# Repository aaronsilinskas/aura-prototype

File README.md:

# Aura Prototype

The prototype firmware and game engine for **Aura**, a platform for interactive
adventure games played in the real world with handheld devices and props that light
up, make sound, and react to how you play. Aura is being built by
[Mindwidgets](https://mindwidgets.com); the site explains what Aura is and
[how it works today](https://mindwidgets.com/aura/how-it-works/).

This repository is where the software is worked out: a game engine that turns
buttons, motion, infrared, and radio into games, and an animation engine for the
lights, sound, and vibration players get back. It is written in Python and runs on
[CircuitPython](https://circuitpython.org/) microcontrollers, and most of it also
runs on a desktop so it can be tested without hardware.

---

## Status

Aura is in prototype. This is working code under active development, not a kit.

- **You can't buy or build an Aura device yet.** There are no build instructions,
  parts list, or finished circuit board designs here. `electronics/` holds only
  rough sketches so far. The prototype is hand-wired from off-the-shelf breakout
  boards.
- **You can read the code, run the tests, and watch the effects in a terminal**
  without any hardware. See [Try it without hardware](#try-it-without-hardware).
- **The games are in `packs/scenes/`**, one folder per scene, alongside scenes for
  testing hardware and browsing effects.

Issues and pull requests are not being sought yet. To hear when there is something
to build or play, sign up at [mindwidgets.com](https://mindwidgets.com).

---

## What is in here

```
effects/      Composable animation engine for lights, sound, and vibration
engine/       Event-driven game loop: rules, scenes, state, packs, and I/O abstractions
packs/        Shared effects and rules, and the scenes (games) built from them
magic/        Spell and aura game logic (elements, buffs and debuffs, cast types)
hardware/     CircuitPython drivers and the hardware abstractions above them
app/          Wires the engine to the hardware and runs a scene on a device
examples/     Entry points: a desktop terminal demo and the on-device scene runner
scripts/      Deploy and maintenance scripts that run on the desktop
electronics/  Circuit board designs (rough sketches only, so far)
docs/         Domain map and architecture decision records (the glossary is GLOSSARY.md)
```

A few words used throughout the code:

- A **rule** is how a game responds to player input, communications, and time.
- An **effect** is what players see, hear, and feel.
- A **scene** is a game: the rules and effects that combine into it.
- A **pack** is a set of rules or effects that more than one scene can use. The
  elemental magic effects (fire, water, lightning, and the rest) are a pack.

See [`docs/domain.md`](docs/domain.md) for key types and constraints, and
[`GLOSSARY.md`](GLOSSARY.md) for the full glossary.

---

## Try it without hardware

You need Python 3.10 or newer and [uv](https://docs.astral.sh/uv/).

```sh
uv sync            # install the development tools
uv run pytest      # run the test suite
```

To watch the effects engine run, start the terminal demo from the repository root
(macOS or Linux, in a terminal with 24-bit color):

```sh
PYTHONPATH=. uv run python examples/ansi-multi-effect-demo.py
```

Press `a` for fire, `b` for water, `c` for lightning, `d` to stop them all, and `q`
to quit.

---

## Hardware the prototype uses

There is no single finished device. The firmware builds whichever of these parts the
device's config file declares, and leaves out the rest:

| Part | What the code supports |
|------|------------------------|
| Microcontroller | RP2350 with PSRAM, running CircuitPython 10. Pimoroni's Pico 2 boards with PSRAM work well, for example the [Pico Plus 2](https://shop.pimoroni.com/products/pimoroni-pico-plus-2) or [Pico LiPo 2](https://shop.pimoroni.com/products/pimoroni-pico-lipo-2). A standard Raspberry Pi Pico 2 has no PSRAM and will not work |
| Lights | IS31FL3741 13×9 RGB LED matrix, NeoPixel strips |
| Sound | I2S audio output |
| Vibration | DRV2605L haptic driver |
| Motion | LIS3DH accelerometer, MMC5603 magnetometer |
| Buttons | Any GPIO pins |
| Infrared | Up to three emitters (line, cone, and area) and one or more receivers |
| Radio | RFM69HCW at 915 MHz |
| Storage | SD card over SPI |

The infrared and radio links were tested with two separate tools,
[infrared-analyzer](https://github.com/aaronsilinskas/infrared-analyzer) and
[rfm69-analyzer](https://github.com/aaronsilinskas/rfm69-analyzer).

---

## Running on a device

These are working notes for a hand-wired prototype, not a build guide.

A device reads two JSON files from the root of its `CIRCUITPY` drive. Both are
required; there are no built-in defaults.

- **`aura-device.json`** declares the hardware: which parts are fitted and which
  pins they use. Each part is built only if its section is present and enabled.
  [`examples/aura-device.pico-2.json`](examples/aura-device.pico-2.json)
  is a complete example, tested on Pimoroni Pico 2 boards.
  [`examples/aura-device.simulated.json`](examples/aura-device.simulated.json)
  is for the test-only Simulated device, not for flashing to a board.
- **`aura-boot.json`** picks the scene to boot, by its folder name under
  `packs/scenes/`, as in
  [`examples/aura-boot.json`](examples/aura-boot.json):
  `{"default_scene": "hardware_test"}`.

  If the device has an SD card, a scene saved to the card's `aura-state.json`
  takes priority over `default_scene`.

To put the code on a board:

1. Install CircuitPython 10 on the board, and copy the Adafruit libraries for the
   parts you declared into `CIRCUITPY/lib/`.
2. Download the matching `mpy-cross` compiler: `scripts/setup_mpy_cross.sh`
3. Copy both JSON files to the `CIRCUITPY` drive.
4. Deploy the scene runner and all modules:

   ```sh
   uv run python -m scripts.deploy examples/hardware/scene_demo.py
   ```

   The board reboots and starts the scene.

### `aura-device.json` in brief

```json
{
  "pixels": [
    {
      "type": "matrix",
      "cols": 13,
      "scope_rows": {
        "global.buff": [0, 1], "global.debuff": [1, 2], "global.main": [2, 5],
        "personal": [5, 7], "directional": [7, 8], "ambient": [8, 9]
      }
    }
  ],
  "buttons": ["GP26", "GP27"],
  "ir": {
    "rx": "GP13",
    "line": "GP10",
    "cone": "GP11",
    "area_of_effect": "GP12"
  },
  "audio": {
    "voices": 2,
    "max_volume": 0.1,
    "i2s_bit_clock": "GP7",
    "i2s_word_select": "GP8",
    "i2s_data": "GP6"
  }
}
```

- **`pixels`** is a list of light outputs. `type` is `"matrix"` (IS31FL3741, at most
  one) or `"neopixel"`. Each entry maps **scopes**, the named regions an effect can
  be shown in, to rows of the matrix (`scope_rows`) or to pixel ranges of a strip
  (`scope_pixels`).
- **`buttons`** is a list of board pin names.
- **`ir`** takes `rx` (one receiver pin, or a list of them) and at least a `line`
  emitter; `cone` and `area_of_effect` emitters are optional. Each scene chooses
  the infrared message format it uses: Aura's own by default, or the `tag` scene's
  format, which works with off-the-shelf infrared tag gear.
- **`audio`** takes `voices` (how many sounds can play at once), `max_volume`
  (0.0 to 1.0), and the three I2S pins.

The example file also shows the `accelerometer`, `magnetometer`, `haptics`, `radio`,
`sdcard`, `i2c`, `spi`, and `neopixel_current_budget` sections.
`neopixel_current_budget` is optional: when the NeoPixel strips could draw more than
`current_limit_ma` at full white, the device dims them at boot to fit, never below
`min_brightness`.

---

## How the engine works

### Event flow

```
(InputEvent | NetworkEvent)
        │
        ▼
   SceneRun               one per running scene: its GameState + rules in dispatch order
        │  run.tick(elapsed)
        ▼
   GameRule.handle_event(event, state)
        │  rules read/write state.get/state.set, queue new events,
        │  call state.effect_controls, call state.scene_controls
        ▼
   EffectManager          routes effects to EffectOutput by scope
        │
        ▼
   EffectOutput           hardware: lights, audio, haptics
```

Rules are stateless: all mutable game data lives in the scene's `GameState`.
Rules fire effects through `state.effect_controls`, read Settings through
`state.settings`, and leave or cover the scene through `state.scene_controls`.

### Packs and scenes

Each folder under `packs/` with a manifest is a pack, and each folder under
`packs/scenes/` is a scene. One scan at boot finds them all and checks every
declaration, so a bad pack or scene fails before anything runs. Pack items are
imported only when first used.

- **Effect pack**: manifest `effects.json`; each `.py` file exports `BUILD`, a
  `(config) → Effect` callable. Effects are named `"pack.effect"`, e.g.
  `"elements.fire"`.
- **Rule pack**: manifest `rules.json`; each `.py` file exports `RULE`, a
  `GameRule` instance. Its manifest can also declare **Settings** and the
  **Capabilities** the rules need:

```json
{
  "version": "1.0",
  "requires": ["button.A", "button.B"],
  "settings": {
    "hold_seconds": {"type": "float", "default": 5.0, "description": "Seconds to hold."}
  }
}
```

A scene is described by its `scene.json`:

```json
{
  "version": "1.0",
  "effect_packs": [{"name": "elements", "version": "1.0"}],
  "rule_packs": [
    {"name": "return_to_lobby", "version": "2.0", "settings": {"hold_seconds": 2.0}}
  ],
  "settings": {
    "window_seconds": {"type": "float", "default": 3.0, "description": "Seconds per window."}
  },
  "requires": ["accelerometer"],
  "ir_codec": "aura"
}
```

| Key | Meaning |
|-----|---------|
| `version` | The scene's own `MAJOR.MINOR` version |
| `effect_packs`, `rule_packs` | Packs in load order. Each `version` is the minimum compatible one: same major, installed minor at least this. A rule pack reference may override that pack's Settings |
| `settings` | Optional. The scene's own Settings, in the manifest's shape |
| `requires` | Optional. Capabilities the scene can't be played without, on top of its rule packs' |
| `ir_codec` | Optional. The infrared message format: `"aura"` (default) or `"tag"` |

A Setting's `type` is `int`, `float`, `bool`, `str` or `list`. One with no
`default` must be set by every scene that uses the pack. Rules read Settings with
`state.settings.get_float("scene", "window_seconds")` and its siblings, by
namespace (`"scene"` or the pack's name).

A **Capability** is hardware a scene can depend on: `button.A` … `button.Z`
(labelled in the order `buttons` lists them), `ir.line`, `ir.cone`,
`ir.area_of_effect`, `ir.receive`, `radio`, `storage`, `accelerometer`,
`magnetometer`. A scene is checked against the device only when it is about to
run. A scene that copes without some hardware leaves it out of `requires` and
asks `state.capabilities.has(name)` instead.

Scenes switch only by rebooting the device into the next one. An **Overlay**
covers a scene for a while and hands it back intact.

The meaning of each term, the versioning rules, and the reasoning behind these
choices are in [`GLOSSARY.md`](GLOSSARY.md) and the ADRs in
[`docs/adr/`](docs/adr/), notably
[ADR-0003](docs/adr/0003-settings-are-declared-as-data-and-checked-at-scan.md)
(Settings),
[ADR-0004](docs/adr/0004-capabilities-are-checked-when-a-scene-is-about-to-run.md)
(Capabilities) and
[ADR-0005](docs/adr/0005-scenes-switch-only-by-reboot.md) (scene switching).

---

## Licensing

This repo splits licensing by area:

- **Software** (`effects/`, `engine/`, `magic/`, `packs/`, `hardware/`, `app/`, `scripts/`, …) —
  [MIT](LICENSE).
- **Hardware designs** (`electronics/`) — CERN-OHL-P-2.0, governed by
  `electronics/LICENSE`.
- **Documentation** (`docs/`) — [CC-BY-4.0](docs/LICENSE).

Each area's `LICENSE` file is authoritative for its scope; `pyproject.toml` declares the
software license for tooling. No per-file license headers are used.

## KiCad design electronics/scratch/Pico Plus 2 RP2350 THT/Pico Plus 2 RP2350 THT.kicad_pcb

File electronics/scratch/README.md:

# Scratch

Freeform experimentation space for electronics design-in-progress — quick sketches,
half-finished schematics, part comparisons, wiring notes, anything that helps while
figuring out what a board should be.

**Nothing in this directory is authoritative.** Nothing here is guaranteed to be
correct, complete, buildable, or even kept up to date. A design in `scratch/` has no
fab tag, no revision folder, and no promise of a `rev<X>/` promotion.

Once a sketch here graduates into an intended real board, it is **promoted** into
`pcbs/<pcb>/rev<X>/` — at that point the `pcbs/` copy is the source of record, and
whatever is left behind in `scratch/` stays non-authoritative. See
`../pcbs/README.md` for the promotion and revision-lifecycle conventions.

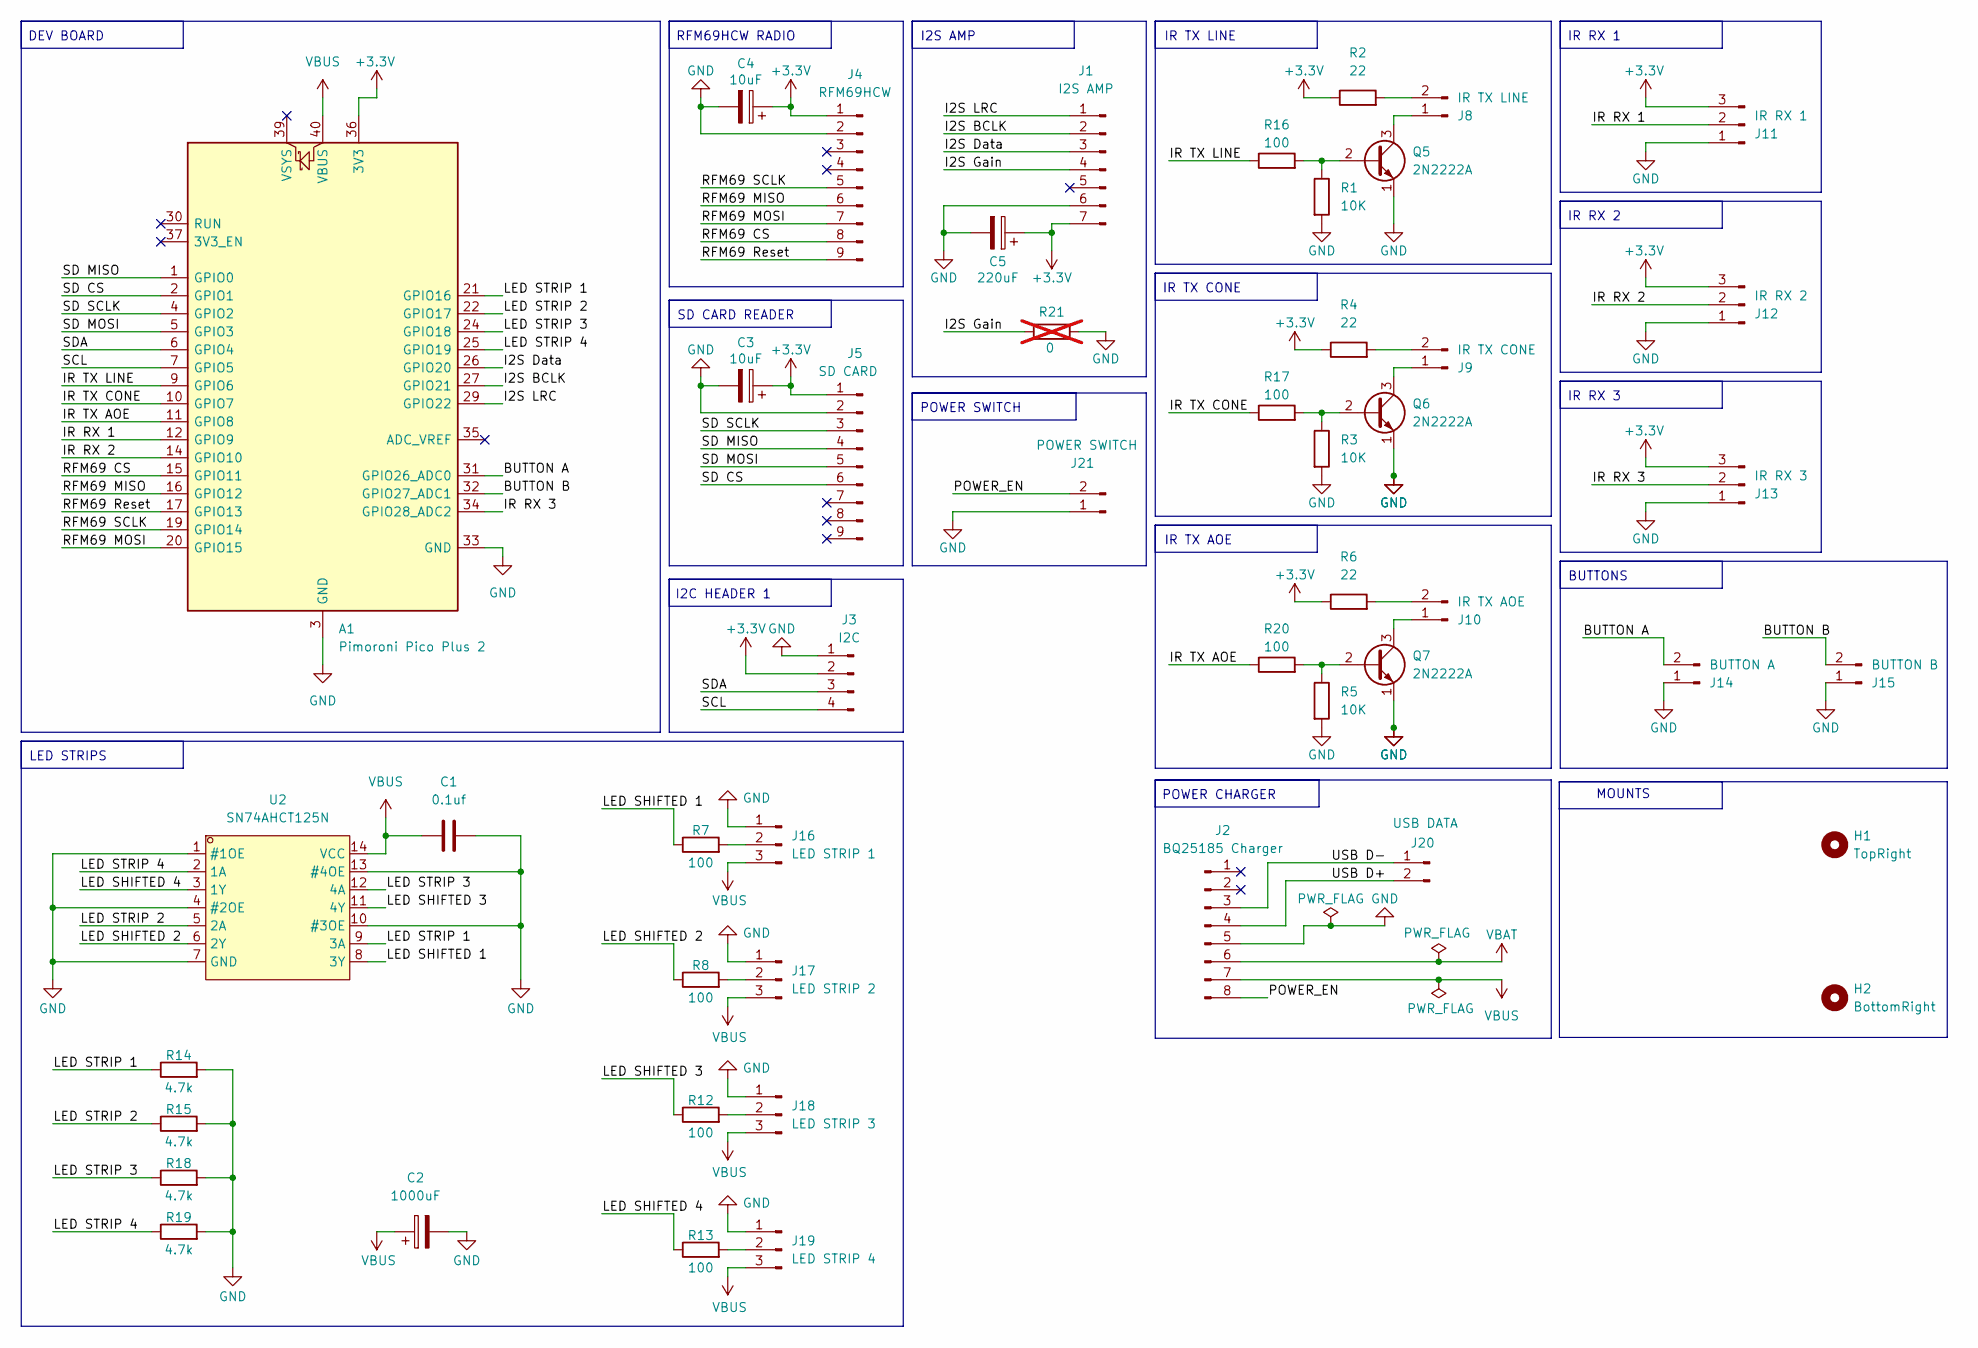
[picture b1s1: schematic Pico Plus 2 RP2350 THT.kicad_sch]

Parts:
A1: Pimoroni Pico Plus 2; RaspberryPi_Pico_Common_Unspecified
C1: 0.1uf; C_Disc_D5.0mm_W2.5mm_P5.00mm
C2: 1000uF; CP_Radial_D8.0mm_P3.80mm
C3, C4: 10uF; CP_Radial_D5.0mm_P2.00mm
C5: 220uF; CP_Radial_D6.3mm_P2.50mm
H1: TopRight; MountingHole_3.2mm_M3_DIN965_Pad
H2: BottomRight; MountingHole_3.2mm_M3_DIN965_Pad
J1: I2S AMP; PinHeader_1x07_P2.54mm_Vertical
J2: BQ25185 Charger; PinHeader_1x08_P2.54mm_Vertical
J3: I2C; PinHeader_1x04_P2.54mm_Vertical
J4: RFM69HCW; PinHeader_1x09_P2.54mm_Vertical
J5: SD CARD; PinHeader_1x09_P2.54mm_Vertical
J8: IR TX LINE; PinHeader_1x02_P2.54mm_Vertical
J9: IR TX CONE; PinHeader_1x02_P2.54mm_Vertical
J10: IR TX AOE; PinHeader_1x02_P2.54mm_Vertical
J11: IR RX 1; PinHeader_1x03_P2.54mm_Vertical
J12: IR RX 2; PinHeader_1x03_P2.54mm_Vertical
J13: IR RX 3; PinHeader_1x03_P2.54mm_Vertical
J14: BUTTON A; PinHeader_1x02_P2.54mm_Vertical
J15: BUTTON B; PinHeader_1x02_P2.54mm_Vertical
J16: LED STRIP 1; PinHeader_1x03_P2.54mm_Vertical
J17: LED STRIP 2; PinHeader_1x03_P2.54mm_Vertical
J18: LED STRIP 3; PinHeader_1x03_P2.54mm_Vertical
J19: LED STRIP 4; PinHeader_1x03_P2.54mm_Vertical
J20: USB DATA; PinHeader_1x02_P2.54mm_Vertical
J21: POWER SWITCH; PinHeader_1x02_P2.54mm_Vertical
Q5, Q6, Q7: 2N2222A; TO-92_Inline
R1, R3, R5: 10K; R_Axial_DIN0207_L6.3mm_D2.5mm_P10.16mm_Horizontal
R2, R4, R6: 22; R_Axial_DIN0207_L6.3mm_D2.5mm_P10.16mm_Horizontal
R7, R8, R12, R13, R16, R17, R20: 100; R_Axial_DIN0207_L6.3mm_D2.5mm_P10.16mm_Horizontal
R14, R15, R18, R19: 4.7k; R_Axial_DIN0207_L6.3mm_D2.5mm_P10.16mm_Horizontal
R21: 0; R_Axial_DIN0207_L6.3mm_D2.5mm_P10.16mm_Horizontal; not fitted
U2: SN74AHCT125N; PDIP-14_L19.3-W6.4-P2.54-LS7.6-BL; MPN SN74AHCT125N; LCSC Part C354152

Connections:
+3.3V: A1.36 (3V3), C3.1, C4.1, C5.1, J1.7, J3.2, J4.1, J5.1, J11.3, J12.3, J13.3, R2.1, R4.1, R6.1
/BUTTON A: A1.31 (GPIO26_ADC0), J14.2
/BUTTON B: A1.32 (GPIO27_ADC1), J15.2
/I2S BCLK: A1.27 (GPIO21), J1.2
/I2S Data: A1.26 (GPIO20), J1.3
/I2S Gain: J1.4, R21.1
/I2S LRC: A1.29 (GPIO22), J1.1
/IR RX 1: A1.12 (GPIO9), J11.2
/IR RX 2: A1.14 (GPIO10), J12.2
/IR RX 3: A1.34 (GPIO28_ADC2), J13.2
/IR TX AOE: A1.11 (GPIO8), R20.1
/IR TX CONE: A1.10 (GPIO7), R17.1
/IR TX LINE: A1.9 (GPIO6), R16.1
/LED SHIFTED 1: R7.1, U2.8 (3Y)
/LED SHIFTED 2: R8.1, U2.6 (2Y)
/LED SHIFTED 3: R12.1, U2.11 (4Y)
/LED SHIFTED 4: R13.1, U2.3 (1Y)
/LED STRIP 1: A1.21 (GPIO16), R14.1, U2.9 (3A)
/LED STRIP 2: A1.22 (GPIO17), R15.1, U2.5 (2A)
/LED STRIP 3: A1.24 (GPIO18), R18.1, U2.12 (4A)
/LED STRIP 4: A1.25 (GPIO19), R19.1, U2.2 (1A)
/POWER_EN: J2.8, J21.2
/RFM69 CS: A1.15 (GPIO11), J4.8
/RFM69 MISO: A1.16 (GPIO12), J4.6
/RFM69 MOSI: A1.20 (GPIO15), J4.7
/RFM69 Reset: A1.17 (GPIO13), J4.9
/RFM69 SCLK: A1.19 (GPIO14), J4.5
/SCL: A1.7 (GPIO5), J3.4
/SD CS: A1.2 (GPIO1), J5.6
/SD MISO: A1.1 (GPIO0), J5.4
/SD MOSI: A1.5 (GPIO3), J5.5
/SD SCLK: A1.4 (GPIO2), J5.3
/SDA: A1.6 (GPIO4), J3.3
/USB D+: J2.4, J20.2
/USB D-: J2.3, J20.1
GND: A1.3 (GND), A1.8 (GND), A1.13 (GND), A1.18 (GND), A1.23 (GND), A1.28 (GND), A1.33 (GND), A1.38 (GND), C1.2, C2.2, C3.2, C4.2, C5.2, J1.6, J2.5, J3.1, J4.2, J5.2, J11.1, J12.1, J13.1, J14.1, J15.1, J16.1, J17.1, J18.1, J19.1, J21.1, Q5.1 (E), Q6.1 (E), Q7.1 (E), R1.2, R3.2, R5.2, R14.2, R15.2, R18.2, R19.2, R21.2, U2.1 (#1OE), U2.4 (#2OE), U2.7 (GND), U2.10 (#3OE), U2.13 (#4OE)
unnamed: J8.1, Q5.3 (C)
unnamed: J8.2, R2.2
unnamed: J9.1, Q6.3 (C)
unnamed: J9.2, R4.2
unnamed: J10.1, Q7.3 (C)
unnamed: J10.2, R6.2
unnamed: J16.2, R7.2
unnamed: J17.2, R8.2
unnamed: J18.2, R12.2
unnamed: J19.2, R13.2
unnamed: Q5.2 (B), R1.1, R16.2
unnamed: Q6.2 (B), R3.1, R17.2
unnamed: Q7.2 (B), R5.1, R20.2
VBAT: J2.6
VBUS: A1.40 (VBUS), C1.1, C2.1, J2.7, J16.3, J17.3, J18.3, J19.3, U2.14 (VCC)

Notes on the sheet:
RFM69HCW RADIO
I2S AMP
SD CARD READER
IR TX AOE
POWER CHARGER
IR TX LINE
POWER SWITCH
MOUNTS
I2C HEADER 1
IR RX 3
BUTTONS
IR RX 1
LED STRIPS
IR TX CONE
DEV BOARD
IR RX 2

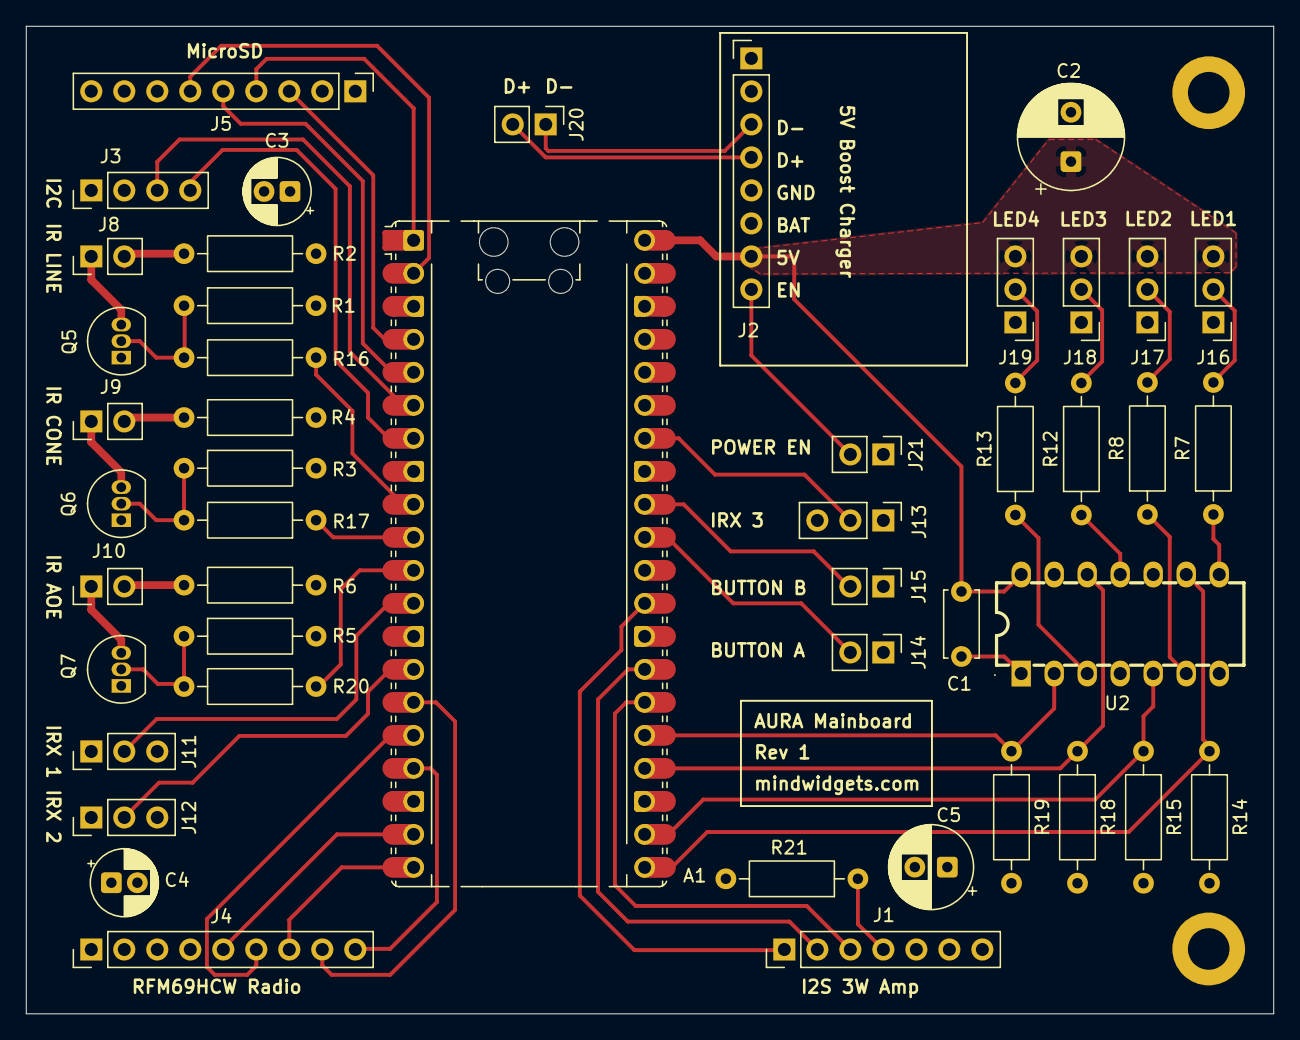
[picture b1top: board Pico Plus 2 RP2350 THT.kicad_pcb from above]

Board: 4 copper layers, 96.0 x 76.0 mm, 49 parts (0 on the bottom side), 50 nets.

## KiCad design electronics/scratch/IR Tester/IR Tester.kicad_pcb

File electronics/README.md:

# Electronics

PCB design source for Aura's custom hardware — schematics, board layouts, shared
symbols/footprints, and fabrication exports. This directory is deliberately separate
from:

- **`hardware/`** (repo root) — the Python firmware package that runs on the props'
  microcontrollers, governed by `ruff`/`import-linter`/`mypy`.
- **CircuitPython's `board` module** — the on-device pin-naming API `hardware/`
  imports at runtime.

`electronics/` contains no Python and is not a package. It carries no import
contracts, isn't touched by `ruff`, `import-linter` or `mypy`, and the Python-only
pre-commit hooks never rewrite the PCB-tool files in here.

Boards are drawn in one of two tools, used as peers: **KiCad** and
**EasyEDA Pro**. Each PCB is committed to a single tool (never mixed within one
board); see `pcbs/README.md`.

---

## Layout

```
electronics/
  README.md      this file — orientation + how to open
  LICENSE        CERN-OHL-P-2.0 (governs everything under electronics/)
  scratch/       freeform, non-authoritative experimentation (see scratch/README.md)
  pcbs/          one subfolder per physical board (see pcbs/README.md)
  libraries/     shared symbols, footprints, and 3D models used across PCBs,
                 split per tool (see libraries/README.md)
```

- **`scratch/`** — sketches and one-off experiments. Nothing in here is
  authoritative; see `scratch/README.md`.
- **`pcbs/`** — the design source of record for every fabricated board, one
  subfolder per PCB. See `pcbs/README.md` for the rev-lifecycle, promotion,
  naming, and fab-tag conventions.
- **`libraries/`** — shared symbol libraries, footprint libraries, and 3D
  models referenced by more than one PCB, so a shared part is edited in one
  place rather than duplicated per board. Split into per-tool subfolders
  (`kicad/`, `easyeda/`) since the two tools' library formats aren't
  interchangeable.

No `<pcb>/` design folders or library files exist yet — this scaffold is
intentionally empty of actual designs.

---

## Revision lifecycle, promotion, and naming (summary)

Full detail lives in `pcbs/README.md`; the short version:

- A **PCB** is the design source for one physical board, named for the board
  itself — never for the prop it ends up in, since a prop and its PCBs are a
  many-to-many relationship (one prop can carry several boards; the same
  board design can serve several props).
- A design **promotes** from `scratch/` into `pcbs/<pcb>/rev<X>/` the moment it
  graduates from sketch to an intended real board. That `rev<X>/` folder is
  then the working directory for the whole design → fab → bring-up → test
  cycle for that revision.
- A genuinely new physical spin of a board is a **new** `rev<X>/` folder
  (`rev2`, `rev3`, …), never an edit-in-place of a prior rev.
- The **rev letter/number goes on the PCB silkscreen**, so the physical board
  and its design folder are always traceable to each other.
- The commit sent to fab is marked with a **git tag** `<pcb>-rev<X>` — the tag,
  not folder immutability, records exactly what was fabricated. Exports are
  hand-generated and refreshed at each fab tag.

---

## How to open

Which tool a board opens in follows its file extensions (`.kicad_*` vs
`.epro`); a board's own folder is drawn in exactly one tool. Tool versions are
pinned so files open without an on-open project upgrade:

- **KiCad** — pinned to **10.0.4** (the latest stable KiCad 10.x release as of
  this writing). Open `pcbs/<pcb>/rev<X>/<pcb>.kicad_pro` in KiCad; schematic
  and PCB editors are reached from there.
- **EasyEDA Pro** — pinned to **3.2**. Open the board's `pcbs/<pcb>/rev<X>/`
  EasyEDA Pro project (`.epro`) in EasyEDA Pro.

> **Note:** no maintainer input was available when this scaffold was created —
> confirm both pinned versions against what the maintainer actually runs, and
> bump these lines deliberately (with a comment on why) whenever the project
> upgrades.

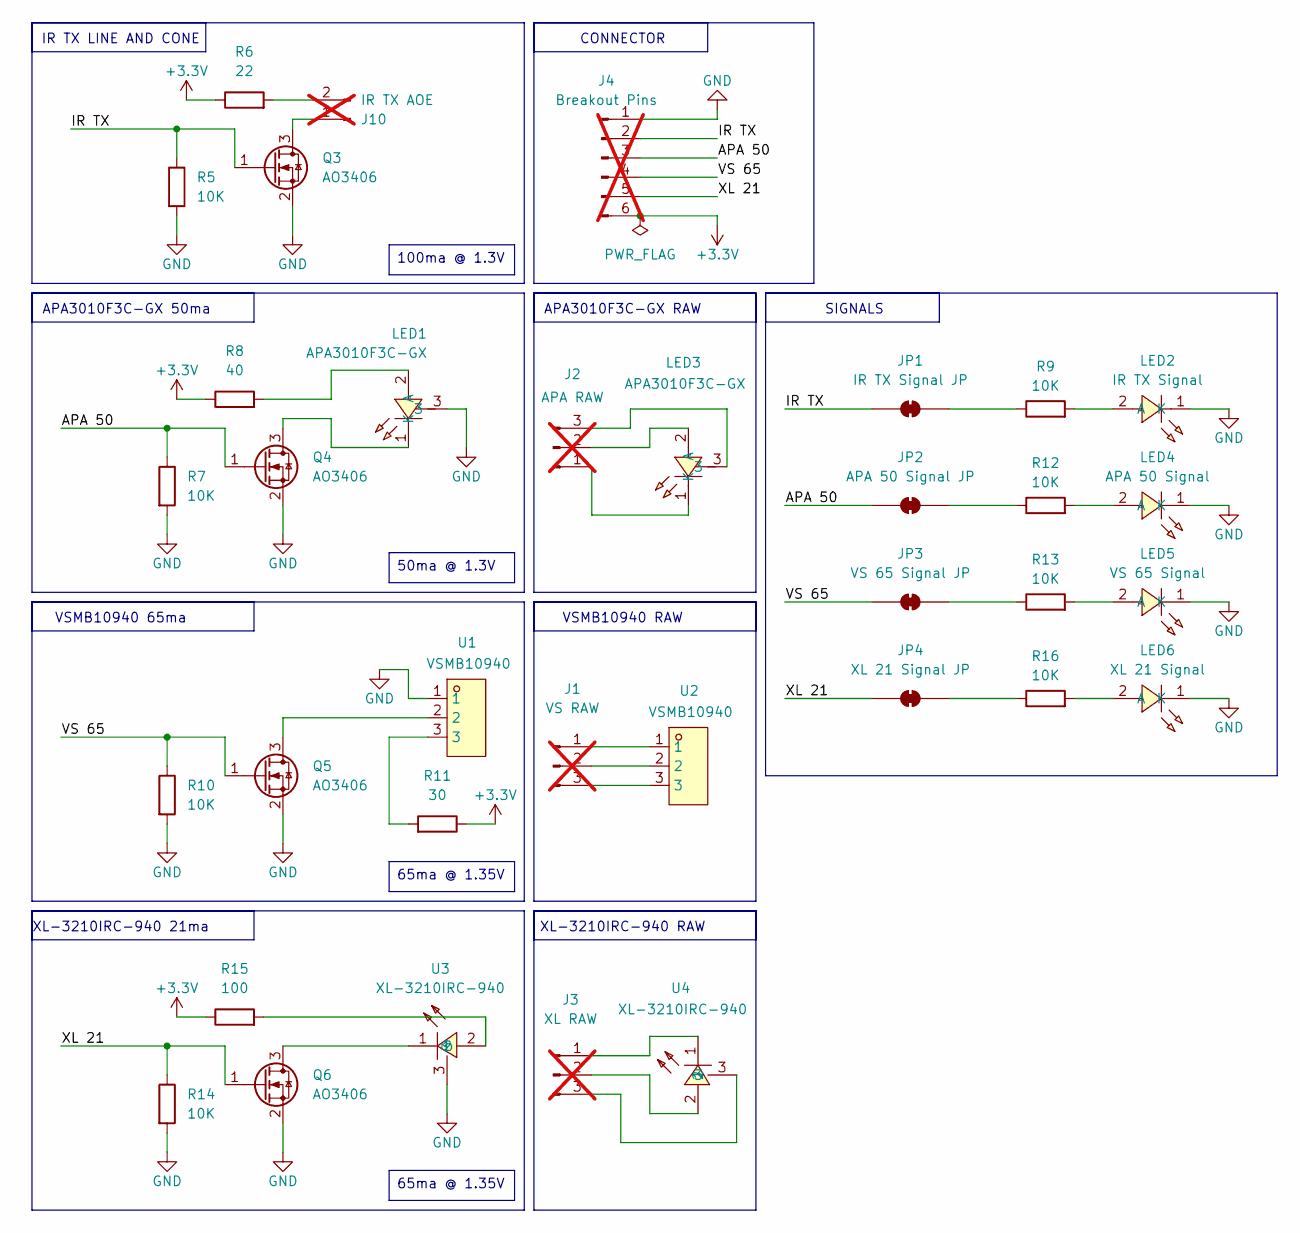
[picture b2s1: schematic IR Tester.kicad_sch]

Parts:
J1: VS RAW; PinHeader_1x03_P2.54mm_Vertical; not fitted
J2: APA RAW; PinHeader_1x03_P2.54mm_Vertical; not fitted
J3: XL RAW; PinHeader_1x03_P2.54mm_Vertical; not fitted
J4: Breakout Pins; PinHeader_1x06_P2.54mm_Vertical; not fitted
J10: IR TX AOE; PinHeader_1x02_P2.54mm_Vertical; not fitted
JP1: IR TX Signal JP; SolderJumper-2_P1.3mm_Bridged_Pad1.0x1.5mm
JP2: APA 50 Signal JP; SolderJumper-2_P1.3mm_Bridged_Pad1.0x1.5mm
JP3: VS 65 Signal JP; SolderJumper-2_P1.3mm_Bridged_Pad1.0x1.5mm
JP4: XL 21 Signal JP; SolderJumper-2_P1.3mm_Bridged_Pad1.0x1.5mm
LED1, LED3: APA3010F3C-GX; LED-SMD_3P-L3.0-W2.0-FD_APA3010F3C; MPN APA3010F3C-GX; LCSC Part C5879342
LED2: IR TX Signal; LED0603-RD_RED; MPN XL-1608SURC-06; LCSC Part C965799
LED4: APA 50 Signal; LED0603-RD_RED; MPN XL-1608SURC-06; LCSC Part C965799
LED5: VS 65 Signal; LED0603-RD_RED; MPN XL-1608SURC-06; LCSC Part C965799
LED6: XL 21 Signal; LED0603-RD_RED; MPN XL-1608SURC-06; LCSC Part C965799
Q3, Q4, Q5, Q6: AO3406; SOT-23; MPN AO3406(ES); LCSC Part C42434120
R5, R7, R9, R10, R12, R13, R14, R16: 10K; R_0805_2012Metric; MPN 0805W8J0103T5E; LCSC Part C25612
R6: 22; R_0805_2012Metric; MPN 0805W8F220JT5E; LCSC Part C17561
R8: 40; R_0805_2012Metric; MPN 0805W8F402JT5E; LCSC Part C17679
R11: 30; R_0805_2012Metric; MPN 0805W8F300JT5E; LCSC Part C17622
R15: 100; R_0805_2012Metric; MPN 0805W8F1000T5E; LCSC Part C17408
U1, U2: VSMB10940; LED-SMD_3P-L3.0-W1.0-FD; MPN VSMB10940; LCSC Part C4749241
U3, U4: XL-3210IRC-940; LED-SMD_3P-L3.2-W1.0-RD_MHS110KGRCT; MPN XL-3210IRC-940; LCSC Part C5349963

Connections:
+3.3V: J4.6, R6.1, R8.1, R11.1, R15.1
/APA 50: J4.3, JP2.1 (A), Q4.1 (G), R7.1
/IR TX: J4.2, JP1.1 (A), Q3.1 (G), R5.1
/VS 65: J4.4, JP3.1 (A), Q5.1 (G), R10.1
/XL 21: J4.5, JP4.1 (A), Q6.1 (G), R14.1
GND: J4.1, LED1.3, LED2.1 (K), LED4.1 (K), LED5.1 (K), LED6.1 (K), Q3.2 (S), Q4.2 (S), Q5.2 (S), Q6.2 (S), R5.2, R7.2, R10.2, R14.2, U1.1, U3.3
unnamed: J1.1, U2.1
unnamed: J1.2, U2.2
unnamed: J1.3, U2.3
unnamed: J2.1, LED3.1 (K)
unnamed: J2.2, LED3.2 (A)
unnamed: J2.3, LED3.3
unnamed: J3.1, U4.1
unnamed: J3.2, U4.2
unnamed: J3.3, U4.3
unnamed: J10.1, Q3.3 (D)
unnamed: J10.2, R6.2
unnamed: JP1.2 (B), R9.1
unnamed: JP2.2 (B), R12.1
unnamed: JP3.2 (B), R13.1
unnamed: JP4.2 (B), R16.1
unnamed: LED1.2 (A), R8.2
unnamed: LED1.1 (K), Q4.3 (D)
unnamed: LED2.2 (A), R9.2
unnamed: LED4.2 (A), R12.2
unnamed: LED5.2 (A), R13.2
unnamed: LED6.2 (A), R16.2
unnamed: Q5.3 (D), U1.2
unnamed: Q6.3 (D), U3.1
unnamed: R11.2, U1.3
unnamed: R15.2, U3.2

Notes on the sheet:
APA3010F3C-GX RAW
APA3010F3C-GX 50ma
VSMB10940 RAW
XL-3210IRC-940 RAW
XL-3210IRC-940 21ma
IR TX LINE AND CONE
SIGNALS
VSMB10940 65ma
CONNECTOR
100ma @ 1.3V
65ma @ 1.35V
50ma @ 1.3V

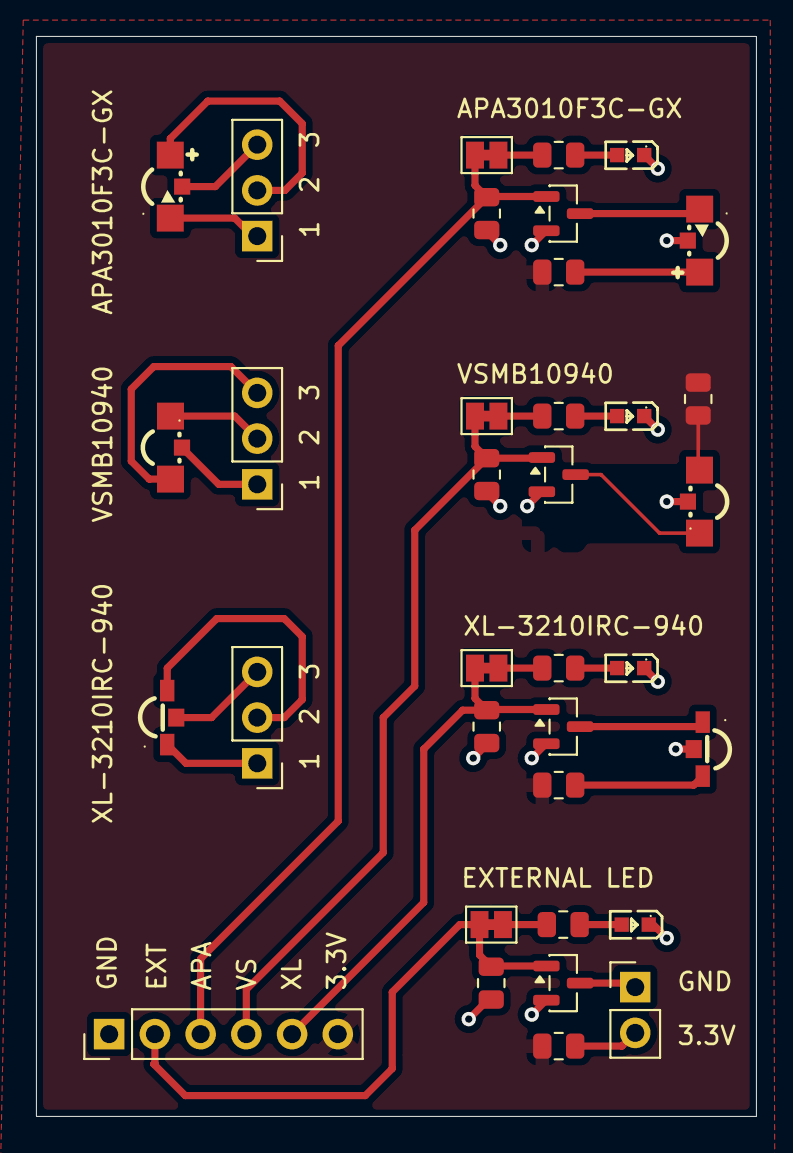
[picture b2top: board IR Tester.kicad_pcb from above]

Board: 2 copper layers, 40.0 x 60.0 mm, 35 parts (0 on the bottom side), 31 nets.

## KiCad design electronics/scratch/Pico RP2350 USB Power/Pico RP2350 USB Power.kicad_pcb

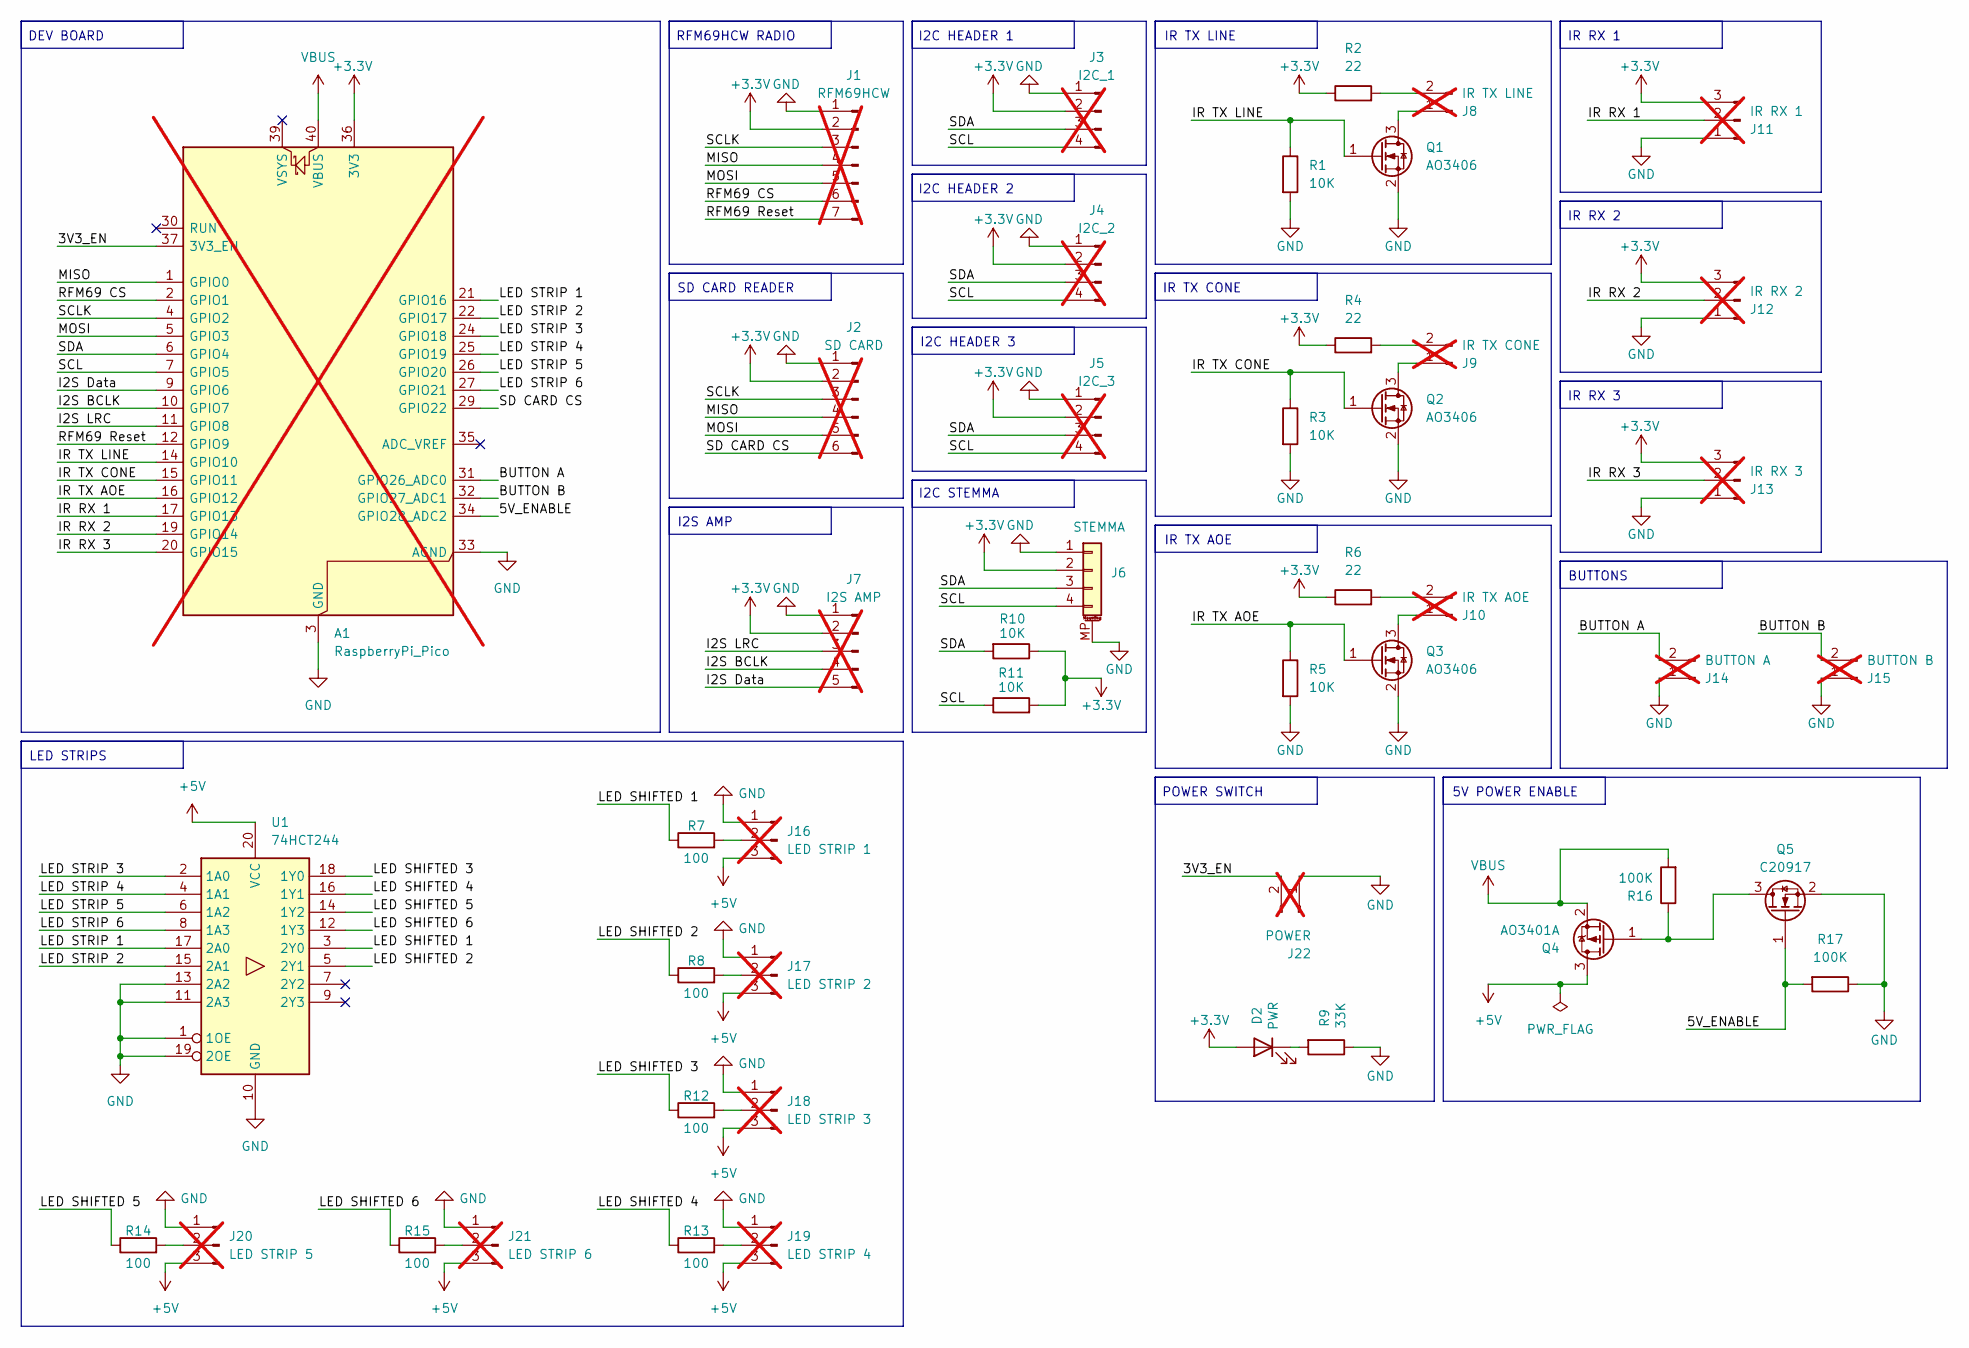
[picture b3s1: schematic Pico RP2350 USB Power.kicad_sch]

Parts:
A1: RaspberryPi_Pico; RaspberryPi_Pico_Common_THT; not fitted
D2: PWR; LED_0805_2012Metric
J1: RFM69HCW; PinHeader_1x07_P2.54mm_Vertical; not fitted
J2: SD CARD; PinHeader_1x06_P2.54mm_Vertical; not fitted
J3: I2C_1; PinHeader_1x04_P2.54mm_Vertical; not fitted
J4: I2C_2; PinHeader_1x04_P2.54mm_Vertical; not fitted
J5: I2C_3; PinHeader_1x04_P2.54mm_Vertical; not fitted
J6: STEMMA; JST_SH_BM04B-SRSS-TB_1x04-1MP_P1.00mm_Vertical
J7: I2S AMP; PinHeader_1x05_P2.54mm_Vertical; not fitted
J8: IR TX LINE; PinHeader_1x02_P2.54mm_Vertical; not fitted
J9: IR TX CONE; PinHeader_1x02_P2.54mm_Vertical; not fitted
J10: IR TX AOE; PinHeader_1x02_P2.54mm_Vertical; not fitted
J11: IR RX 1; PinHeader_1x03_P2.54mm_Vertical; not fitted
J12: IR RX 2; PinHeader_1x03_P2.54mm_Vertical; not fitted
J13: IR RX 3; PinHeader_1x03_P2.54mm_Vertical; not fitted
J14: BUTTON A; PinHeader_1x02_P2.54mm_Vertical; not fitted
J15: BUTTON B; PinHeader_1x02_P2.54mm_Vertical; not fitted
J16: LED STRIP 1; PinHeader_1x03_P2.54mm_Vertical; not fitted
J17: LED STRIP 2; PinHeader_1x03_P2.54mm_Vertical; not fitted
J18: LED STRIP 3; PinHeader_1x03_P2.54mm_Vertical; not fitted
J19: LED STRIP 4; PinHeader_1x03_P2.54mm_Vertical; not fitted
J20: LED STRIP 5; PinHeader_1x03_P2.54mm_Vertical; not fitted
J21: LED STRIP 6; PinHeader_1x03_P2.54mm_Vertical; not fitted
J22: POWER; PinHeader_1x02_P2.54mm_Vertical; not fitted
Q1, Q2, Q3: AO3406; SOT-23
Q4: AO3401A; SOT-23
Q5: C20917; SOT-23
R1, R3, R5, R10, R11: 10K; R_0805_2012Metric
R2, R4, R6: 22; R_0805_2012Metric
R7, R8, R12, R13, R14, R15: 100; R_0805_2012Metric
R9: 33K; R_0805_2012Metric
R16, R17: 100K; R_0805_2012Metric
U1: 74HCT244; TSSOP-20_4.4x6.5mm_P0.65mm

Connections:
+3.3V: A1.36 (3V3), D2.2 (A), J1.2, J2.2, J3.2, J4.2, J5.2, J6.2, J7.2, J11.3, J12.3, J13.3, R2.1, R4.1, R6.1, R10.1, R11.2
+5V: J16.3, J17.3, J18.3, J19.3, J20.3, J21.3, Q4.3 (D), U1.20 (VCC)
/3V3_EN: A1.37 (3V3_EN), J22.2
/5V_ENABLE: A1.34 (GPIO28_ADC2), Q5.1 (G), R17.2
/BUTTON A: A1.31 (GPIO26_ADC0), J14.2
/BUTTON B: A1.32 (GPIO27_ADC1), J15.2
/I2S BCLK: A1.10 (GPIO7), J7.4
/I2S Data: A1.9 (GPIO6), J7.5
/I2S LRC: A1.11 (GPIO8), J7.3
/IR RX 1: A1.17 (GPIO13), J11.2
/IR RX 2: A1.19 (GPIO14), J12.2
/IR RX 3: A1.20 (GPIO15), J13.2
/IR TX AOE: A1.16 (GPIO12), Q3.1 (G), R5.1
/IR TX CONE: A1.15 (GPIO11), Q2.1 (G), R3.1
/IR TX LINE: A1.14 (GPIO10), Q1.1 (G), R1.1
/LED SHIFTED 1: R7.1, U1.3 (2Y0)
/LED SHIFTED 2: R8.1, U1.5 (2Y1)
/LED SHIFTED 3: R12.1, U1.18 (1Y0)
/LED SHIFTED 4: R13.1, U1.16 (1Y1)
/LED SHIFTED 5: R14.1, U1.14 (1Y2)
/LED SHIFTED 6: R15.1, U1.12 (1Y3)
/LED STRIP 1: A1.21 (GPIO16), U1.17 (2A0)
/LED STRIP 2: A1.22 (GPIO17), U1.15 (2A1)
/LED STRIP 3: A1.24 (GPIO18), U1.2 (1A0)
/LED STRIP 4: A1.25 (GPIO19), U1.4 (1A1)
/LED STRIP 5: A1.26 (GPIO20), U1.6 (1A2)
/LED STRIP 6: A1.27 (GPIO21), U1.8 (1A3)
/MISO: A1.1 (GPIO0), J1.4, J2.4
/MOSI: A1.5 (GPIO3), J1.5, J2.5
/RFM69 CS: A1.2 (GPIO1), J1.6
/RFM69 Reset: A1.12 (GPIO9), J1.7
/SCL: A1.7 (GPIO5), J3.4, J4.4, J5.4, J6.4, R11.1
/SCLK: A1.4 (GPIO2), J1.3, J2.3
/SD CARD CS: A1.29 (GPIO22), J2.6
/SDA: A1.6 (GPIO4), J3.3, J4.3, J5.3, J6.3, R10.2
GND: A1.3 (GND), A1.8 (GND), A1.13 (GND), A1.18 (GND), A1.23 (GND), A1.28 (GND), A1.33 (AGND), A1.38 (GND), J1.1, J2.1, J3.1, J4.1, J5.1, J6.1, J6.MP (MountPin), J7.1, J11.1, J12.1, J13.1, J14.1, J15.1, J16.1, J17.1, J18.1, J19.1, J20.1, J21.1, J22.1, Q1.2 (S), Q2.2 (S), Q3.2 (S), Q5.2 (S), R1.2, R3.2, R5.2, R9.1, R17.1, U1.1 (1OE), U1.10 (GND), U1.11 (2A3), U1.13 (2A2), U1.19 (2OE)
unnamed: D2.1 (K), R9.2
unnamed: J8.1, Q1.3 (D)
unnamed: J8.2, R2.2
unnamed: J9.1, Q2.3 (D)
unnamed: J9.2, R4.2
unnamed: J10.1, Q3.3 (D)
unnamed: J10.2, R6.2
unnamed: J16.2, R7.2
unnamed: J17.2, R8.2
unnamed: J18.2, R12.2
unnamed: J19.2, R13.2
unnamed: J20.2, R14.2
unnamed: J21.2, R15.2
unnamed: Q4.1 (G), Q5.3 (D), R16.1
VBUS: A1.40 (VBUS), Q4.2 (S), R16.2

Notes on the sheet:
IR TX AOE
IR RX 2
I2C HEADER 2
SD CARD READER
I2C STEMMA
IR TX LINE
LED STRIPS
IR RX 1
IR TX CONE
BUTTONS
POWER SWITCH
5V POWER ENABLE
I2S AMP
IR RX 3
I2C HEADER 3
RFM69HCW RADIO
I2C HEADER 1
DEV BOARD

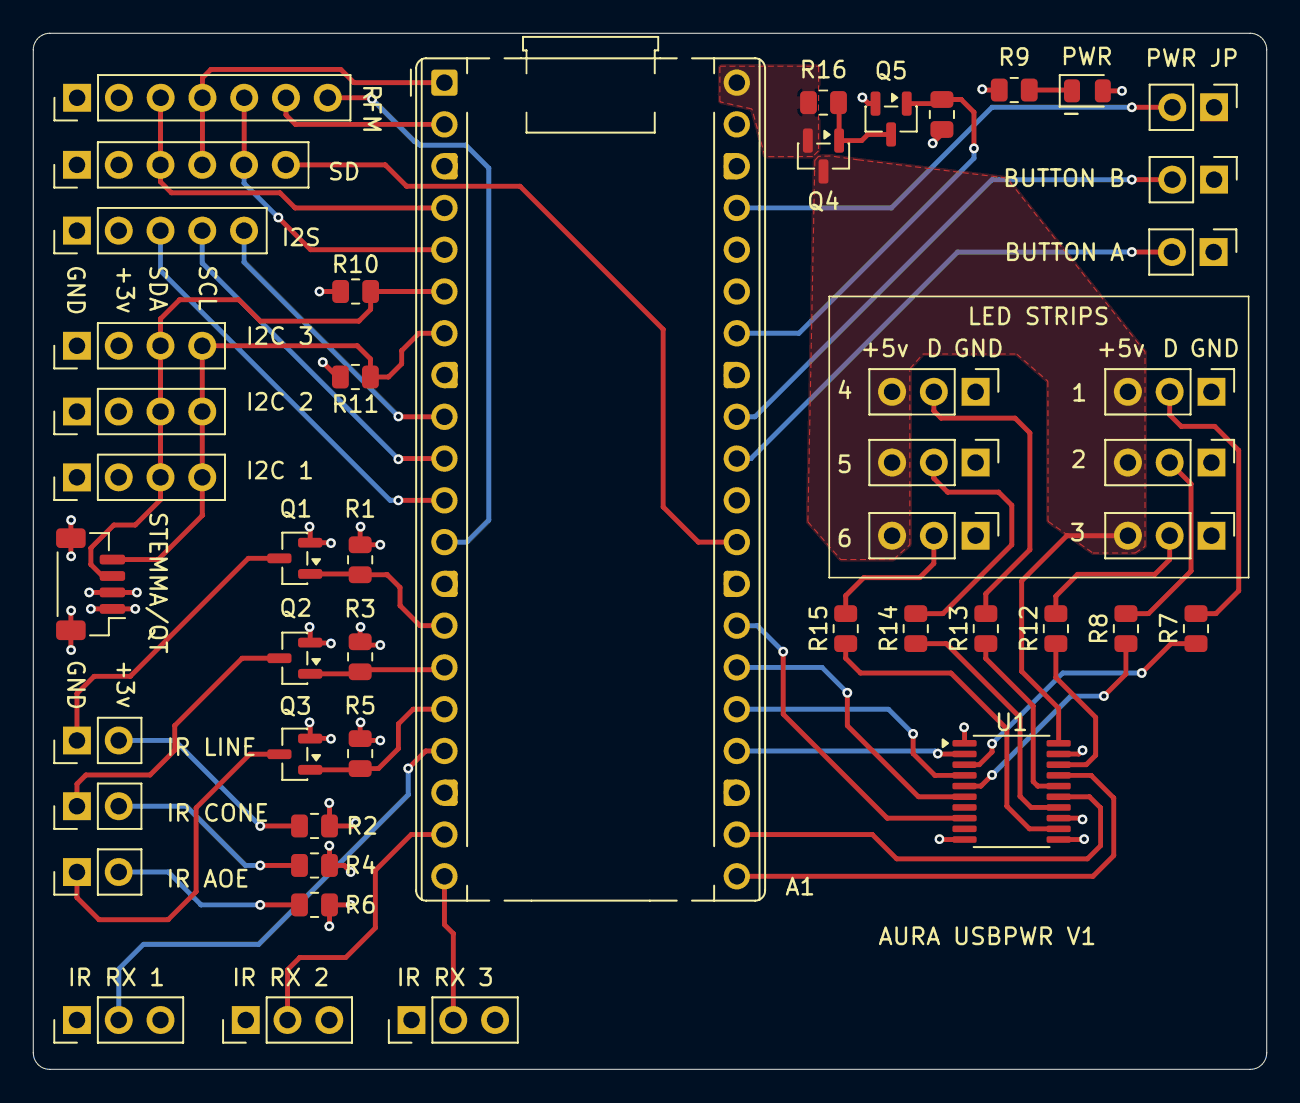
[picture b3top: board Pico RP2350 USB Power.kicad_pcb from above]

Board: 4 copper layers, 75.0 x 63.0 mm, 47 parts (0 on the bottom side), 51 nets.
